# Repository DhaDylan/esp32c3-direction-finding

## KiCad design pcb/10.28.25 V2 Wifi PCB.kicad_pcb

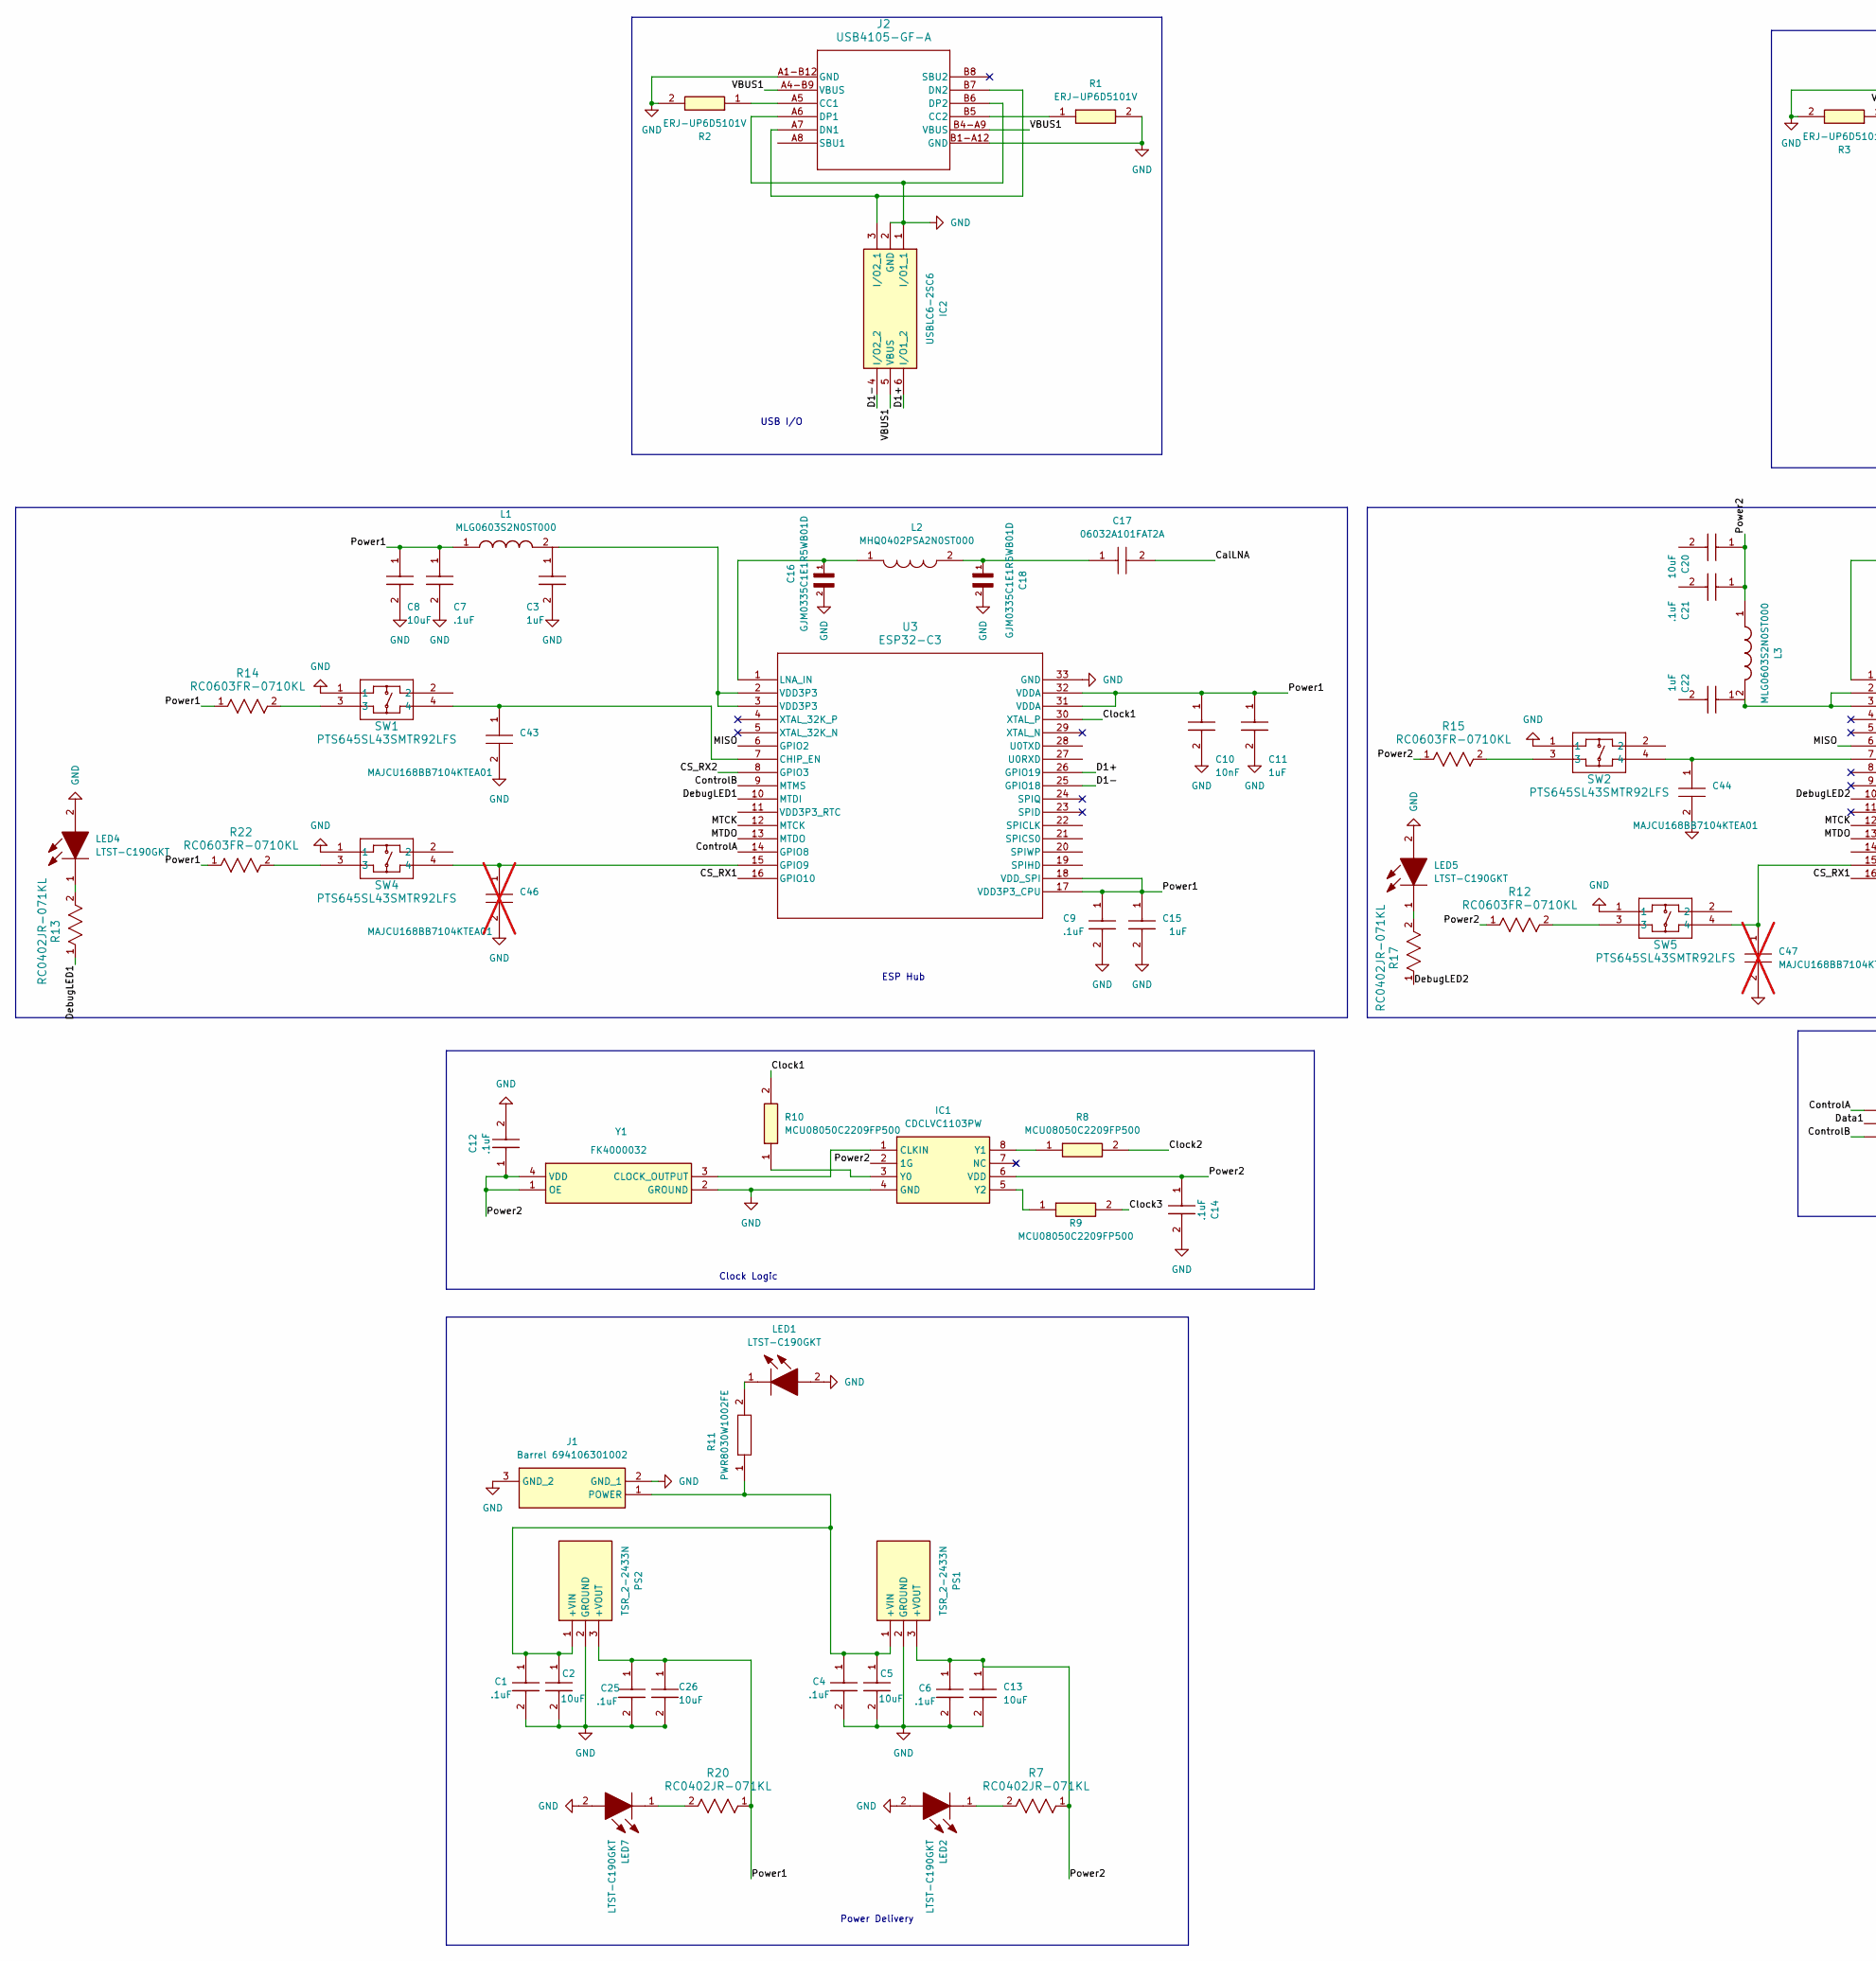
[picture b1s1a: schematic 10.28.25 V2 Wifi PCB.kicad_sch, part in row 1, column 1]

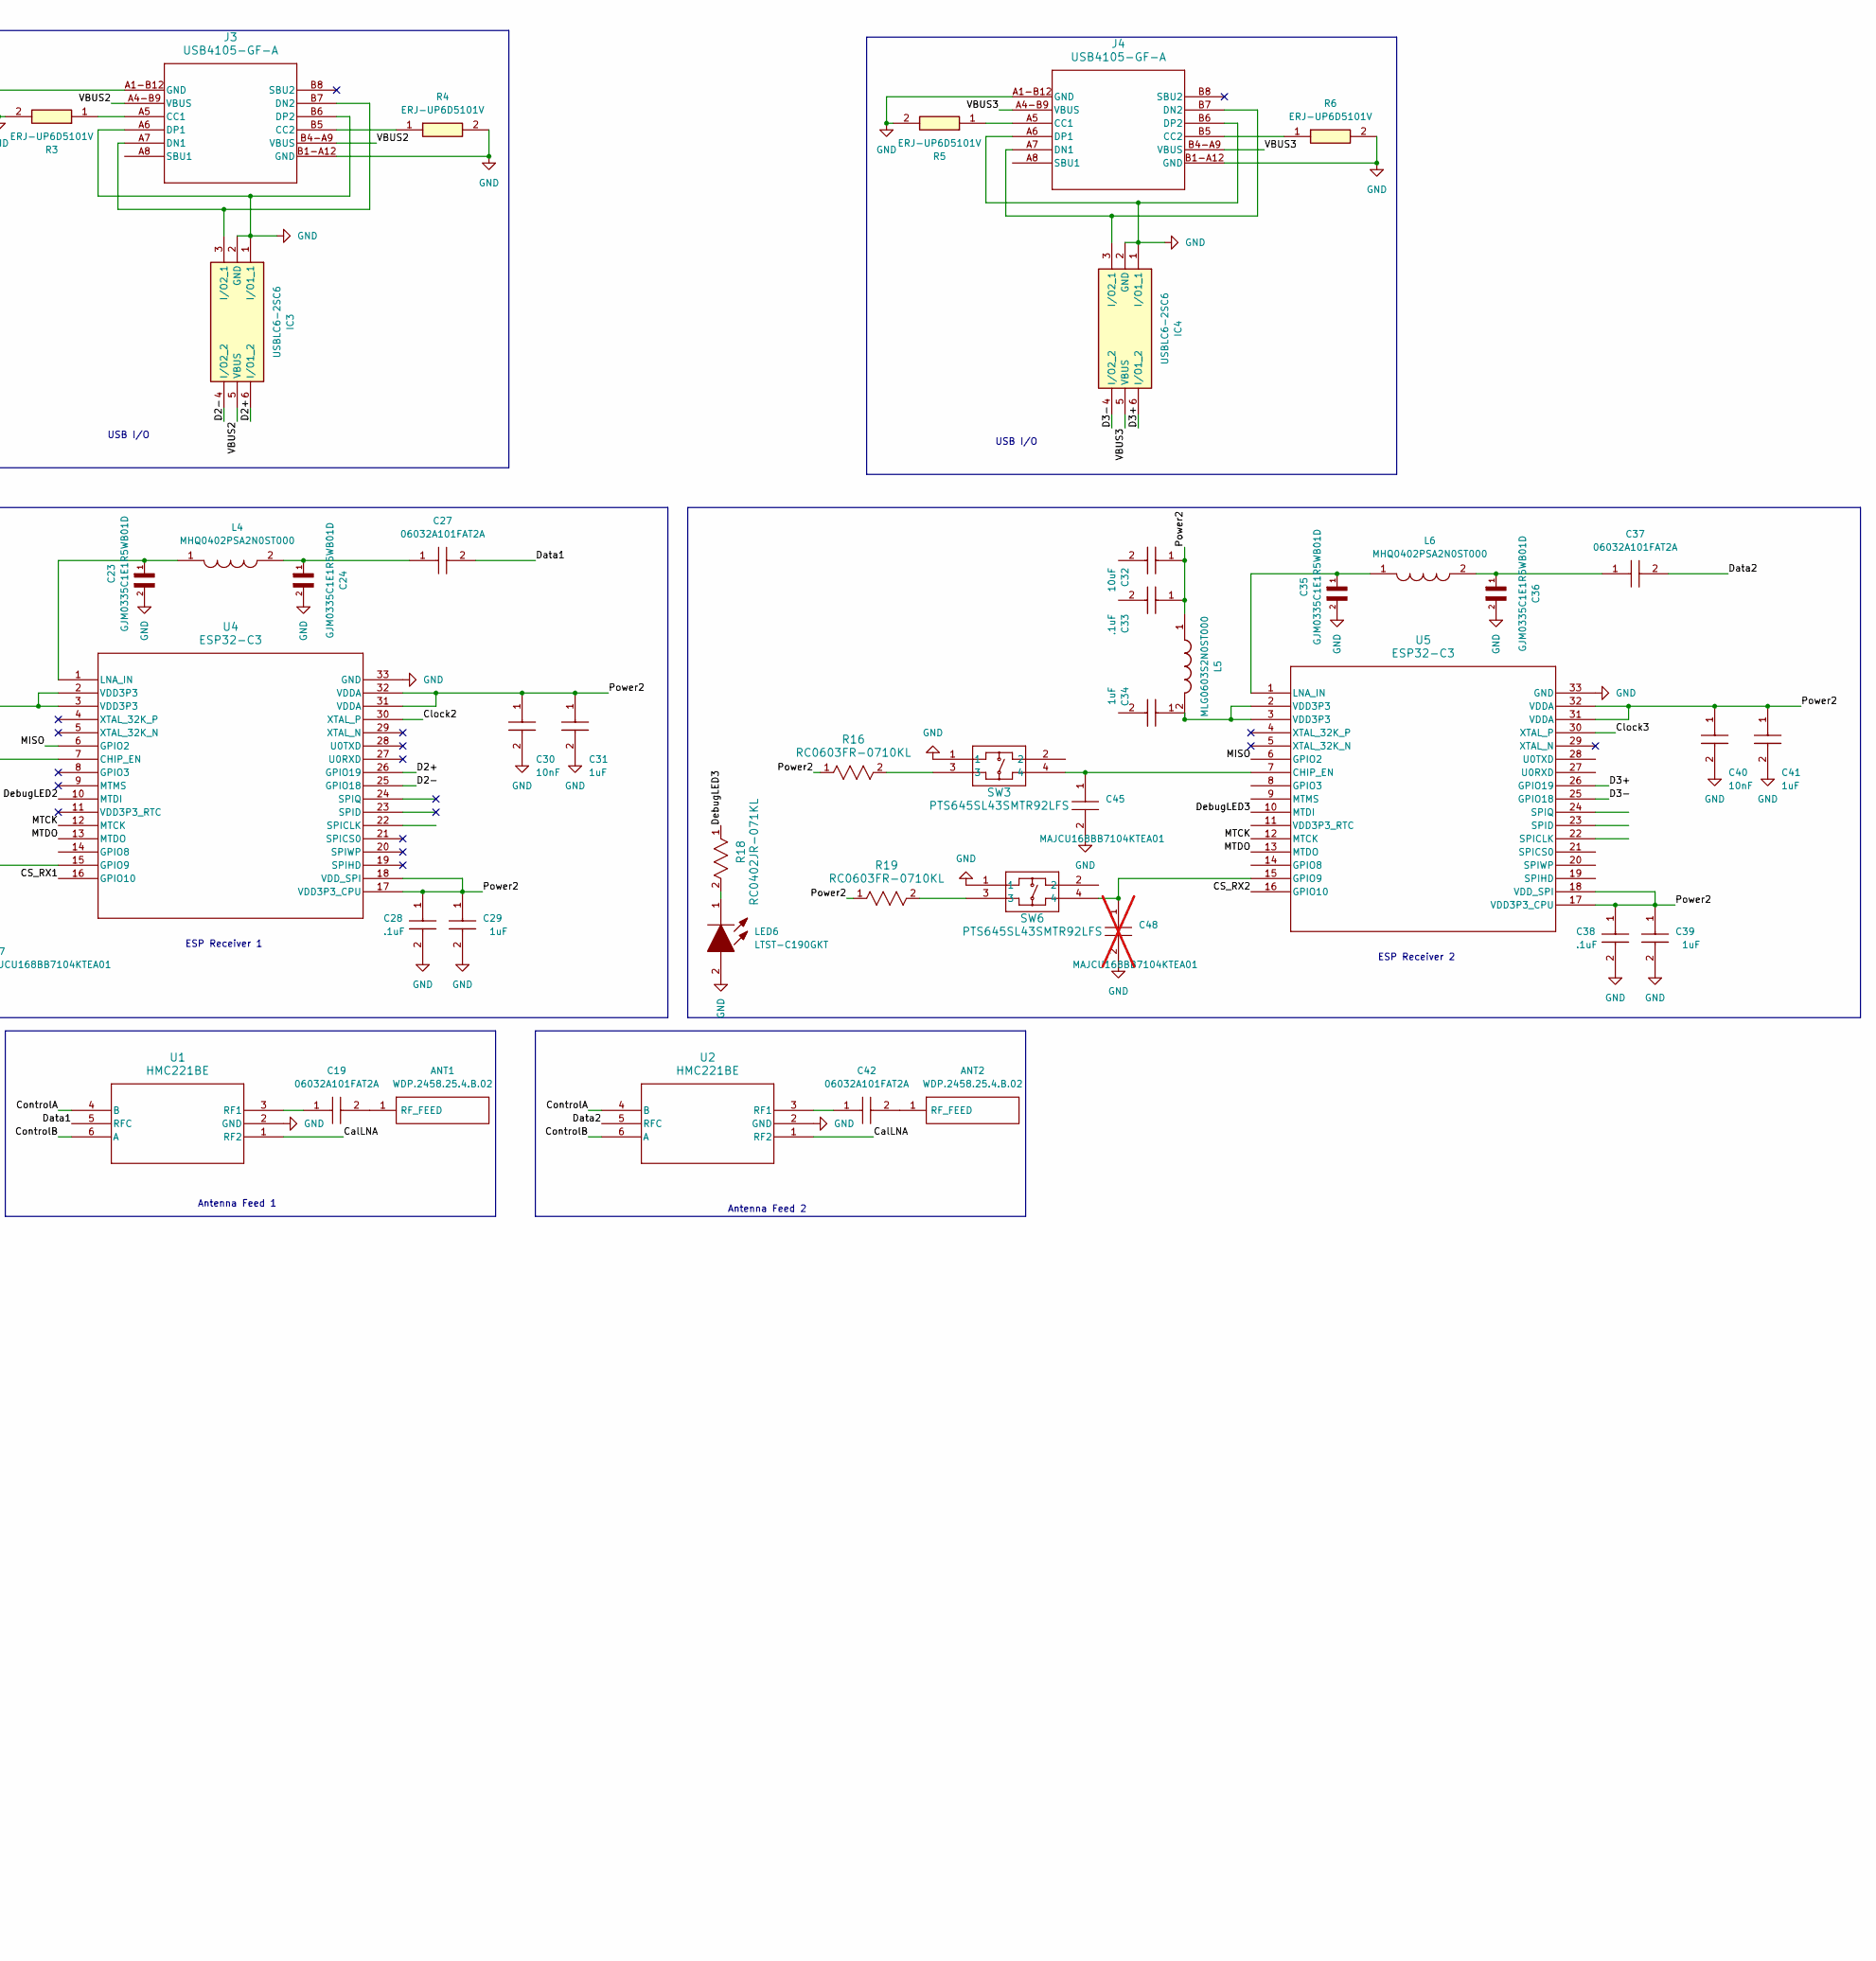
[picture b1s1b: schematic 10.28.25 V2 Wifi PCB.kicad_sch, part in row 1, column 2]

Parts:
ANT1, ANT2: WDP.2458.25.4.B.02; WDP2458254B02; Mouser Part Number 960-WDP.2458.25.4B02
C1, C4, C6, C7, C9, C12, C14, C21, C25, C28, C33, C38: .1uF; MBASx21x; Manufacturer_Part_Number MBASQ21GAB7104MTCA01
C2, C5, C8, C13, C20, C26, C32: 10uF; CAPC1608X80N; Mouser Part Number 810-C1608X7T1A106M08
C3, C11, C15, C22, C29, C31, C34, C39, C41: 1uF; CAPC1608X90N; Manufacturer_Part_Number CGA3E3X7R1H105K080AB
C10, C30, C40: 10nF; CAPC1608X90N; Mouser Part Number 581-0603YC103M4T2A
C16, C18, C23, C24, C35, C36: GJM0335C1E1R5WB01D; CAPC0603X33N
C17, C19, C27, C37, C42: 06032A101FAT2A; CAPC1608X90N; Mouser Part Number 581-06032A101FAT2A
C43, C44, C45: MAJCU168BB7104KTEA01; MAJx16; Manufacturer_Part_Number MAJCU168BB7104KTEA01
C46, C47, C48: MAJCU168BB7104KTEA01; MAJx16; Manufacturer_Part_Number MAJCU168BB7104KTEA01; not fitted
IC1: CDCLVC1103PW; SOP65P640X120-8N; Mouser Part Number 595-CDCLVC1103PW
IC2, IC3, IC4: USBLC6-2SC6; SOT95P280X145-6N; Mouser Part Number 511-USBLC6-2SC6
J1: Barrel 694106301002; 694106301002_1; Mouser Part Number 710-694106301002
J2, J3, J4: USB4105-GF-A; USB4105_GCT
L1, L3, L5: MLG0603S2N0ST000; MLG0603S; Manufacturer_Part_Number MLG0603S2N0ST000
L2, L4, L6: MHQ0402PSA2N0ST000; INDC0402X26N; Mouser Part Number 810-MHQ0402PSA2N0ST0
LED1, LED2, LED4, LED5, LED6, LED7: LTST-C190GKT; LEDC1608X90N; Mouser Part Number 859-LTST-C190GKT
PS1, PS2: TSR_2-2433N; TSR22433N; Manufacturer_Part_Number TSR 2-2433N
R1, R2, R3, R4, R5, R6: ERJ-UP6D5101V; ERJUP6; Mouser Part Number 667-ERJ-UP6D5101V
R7, R13, R17, R18, R20: RC0402JR-071KL; RC0402N_YAG
R8, R9, R10: MCU08050C2209FP500; RESC2012X55N; Mouser Part Number 594-MCU08050C2209FP5
R11: PWR8030W1002FE; RESM20876X785N; Mouser Part Number 652-PWR8030W1002FE
R12, R14, R15, R16, R19, R22: RC0603FR-0710KL; RC0603N_YAG
SW1, SW2, SW3, SW4, SW5, SW6: PTS645SL43SMTR92LFS; PTS645SL43SMTR92LFS_CNK
U1, U2: HMC221BE; RJ-6_ADI
U3, U4, U5: ESP32-C3; QFN32_5X5_EXP
Y1: FK4000032; Mouser Part Number 729-FK4000032

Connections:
/CS_RX1: U3.16 (GPIO10), U4.16 (GPIO10)
/CS_RX2: U3.8 (GPIO3), U5.16 (GPIO10)
/CalLNA: C17.2, U1.1 (RF2), U2.1 (RF2)
/Clock1: R10.2, U3.30 (XTAL_P)
/Clock2: R8.2, U4.30 (XTAL_P)
/Clock3: R9.2, U5.30 (XTAL_P)
/ControlA: U1.4 (B), U2.4 (B), U3.14 (GPIO8)
/ControlB: U1.6 (A), U2.6 (A), U3.9 (MTMS)
/D1+: IC2.6 (I/O1_2), U3.26 (GPIO19)
/D1-: IC2.4 (I/O2_2), U3.25 (GPIO18)
/D2+: IC3.6 (I/O1_2), U4.26 (GPIO19)
/D2-: IC3.4 (I/O2_2), U4.25 (GPIO18)
/D3+: IC4.6 (I/O1_2), U5.26 (GPIO19)
/D3-: IC4.4 (I/O2_2), U5.25 (GPIO18)
/Data1: C27.2, U1.5 (RFC)
/Data2: C37.2, U2.5 (RFC)
/DebugLED1: R13.1, U3.10 (MTDI)
/DebugLED2: R17.1, U4.10 (MTDI)
/DebugLED3: R18.1, U5.10 (MTDI)
/MISO: U3.6 (GPIO2), U4.6 (GPIO2), U5.6 (GPIO2)
/MTCK: U3.12 (MTCK), U4.12 (MTCK), U5.12 (MTCK)
/MTDO: U3.13 (MTDO), U4.13 (MTDO), U5.13 (MTDO)
/Power1: C7.1, C8.1, C9.1, C10.1, C11.1, C15.1, C25.1, C26.1, L1.1, PS2.3 (+VOUT), R14.1, R20.1, R22.1, U3.17 (VDD3P3_CPU), U3.18 (VDD_SPI), U3.31 (VDDA), U3.32 (VDDA)
/Power2: C6.1, C12.1, C13.1, C14.1, C20.1, C21.1, C28.1, C29.1, C30.1, C31.1, C32.1, C33.1, C38.1, C39.1, C40.1, C41.1, IC1.2 (1G), IC1.6 (VDD), L3.1, L5.1, PS1.3 (+VOUT), R7.1, R12.1, R15.1, R16.1, R19.1, U4.17 (VDD3P3_CPU), U4.18 (VDD_SPI), U4.31 (VDDA), U4.32 (VDDA), U5.17 (VDD3P3_CPU), U5.18 (VDD_SPI), U5.31 (VDDA), U5.32 (VDDA), Y1.1 (OE), Y1.4 (VDD)
/VBUS1: IC2.5 (VBUS), J2.A4-B9 (VBUS), J2.B4-A9 (VBUS)
/VBUS2: IC3.5 (VBUS), J3.A4-B9 (VBUS), J3.B4-A9 (VBUS)
/VBUS3: IC4.5 (VBUS), J4.A4-B9 (VBUS), J4.B4-A9 (VBUS)
GND: C1.2, C2.2, C3.2, C4.2, C5.2, C6.2, C7.2, C8.2, C9.2, C10.2, C11.2, C12.2, C13.2, C14.2, C15.2, C16.2, C18.2, C23.2, C24.2, C25.2, C26.2, C28.2, C29.2, C30.2, C31.2, C35.2, C36.2, C38.2, C39.2, C40.2, C41.2, C43.2, C44.2, C45.2, C46.2, C47.2, C48.2, IC1.4 (GND), IC2.1 (I/O1_1), IC2.2 (GND), IC3.1 (I/O1_1), IC3.2 (GND), IC4.1 (I/O1_1), IC4.2 (GND), J1.2 (GND_1), J1.3 (GND_2), J2.A1-B12 (GND), J2.A6 (DP1), J2.B1-A12 (GND), J2.B6 (DP2), J3.A1-B12 (GND), J3.A6 (DP1), J3.B1-A12 (GND), J3.B6 (DP2), J4.A1-B12 (GND), J4.A6 (DP1), J4.B1-A12 (GND), J4.B6 (DP2), LED1.2, LED2.2, LED4.2, LED5.2, LED6.2, LED7.2, PS1.2 (GROUND), PS2.2 (GROUND), R1.2, R2.2, R3.2, R4.2, R5.2, R6.2, SW1.1, SW2.1, SW3.1, SW4.1, SW5.1, SW6.1, U1.2 (GND), U2.2 (GND), U3.33 (GND), U4.33 (GND), U5.33 (GND), Y1.2 (GROUND)
unnamed: ANT1.1 (RF_FEED), C19.2
unnamed: ANT2.1 (RF_FEED), C42.2
unnamed: C17.1, C18.1, L2.2
unnamed: C22.1, L3.2, U4.2 (VDD3P3), U4.3 (VDD3P3)
unnamed: C24.1, C27.1, L4.2
unnamed: C34.1, L5.2, U5.2 (VDD3P3), U5.3 (VDD3P3)
unnamed: C36.1, C37.1, L6.2
unnamed: IC1.1 (CLKIN), Y1.3 (CLOCK_OUTPUT)
unnamed: IC1.3 (Y0), R10.1
unnamed: IC1.8 (Y1), R8.1
unnamed: IC1.5 (Y2), R9.1
unnamed: IC2.3 (I/O2_1), J2.A7 (DN1), J2.B7 (DN2)
unnamed: IC3.3 (I/O2_1), J3.A7 (DN1), J3.B7 (DN2)
unnamed: IC4.3 (I/O2_1), J4.A7 (DN1), J4.B7 (DN2)
unnamed: C1.1, C2.1, C4.1, C5.1, J1.1 (POWER), PS1.1 (+VIN), PS2.1 (+VIN), R11.1
unnamed: J2.A5 (CC1), R2.1
unnamed: J2.B5 (CC2), R1.1
unnamed: J3.A5 (CC1), R3.1
unnamed: J3.B5 (CC2), R4.1
unnamed: J4.A5 (CC1), R5.1
unnamed: J4.B5 (CC2), R6.1
unnamed: L1.2, U3.2 (VDD3P3), U3.3 (VDD3P3)
unnamed: LED1.1, R11.2
unnamed: LED2.1, R7.2
unnamed: LED4.1, R13.2
unnamed: LED5.1, R17.2
unnamed: LED6.1, R18.2
unnamed: LED7.1, R20.2
unnamed: R12.2, SW5.3
unnamed: R14.2, SW1.3
unnamed: R15.2, SW2.3
unnamed: R16.2, SW3.3
unnamed: R19.2, SW6.3
unnamed: R22.2, SW4.3
unnamed: C19.1, U1.3 (RF1)
unnamed: C42.1, U2.3 (RF1)
unnamed: C43.1, SW1.4, U3.7 (CHIP_EN)
unnamed: C46.1, SW4.4, U3.15 (GPIO9)
unnamed: C16.1, L2.1, U3.1 (LNA_IN)
unnamed: C44.1, SW2.4, U4.7 (CHIP_EN)
unnamed: C47.1, SW5.4, U4.15 (GPIO9)
unnamed: C23.1, L4.1, U4.1 (LNA_IN)
unnamed: C45.1, SW3.4, U5.7 (CHIP_EN)
unnamed: C48.1, SW6.4, U5.15 (GPIO9)
unnamed: C35.1, L6.1, U5.1 (LNA_IN)

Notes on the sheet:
Antenna Feed 1
USB I/O
Clock Logic
ESP Hub
Antenna Feed 2
ESP Receiver 2
ESP Receiver 1
Power Delivery

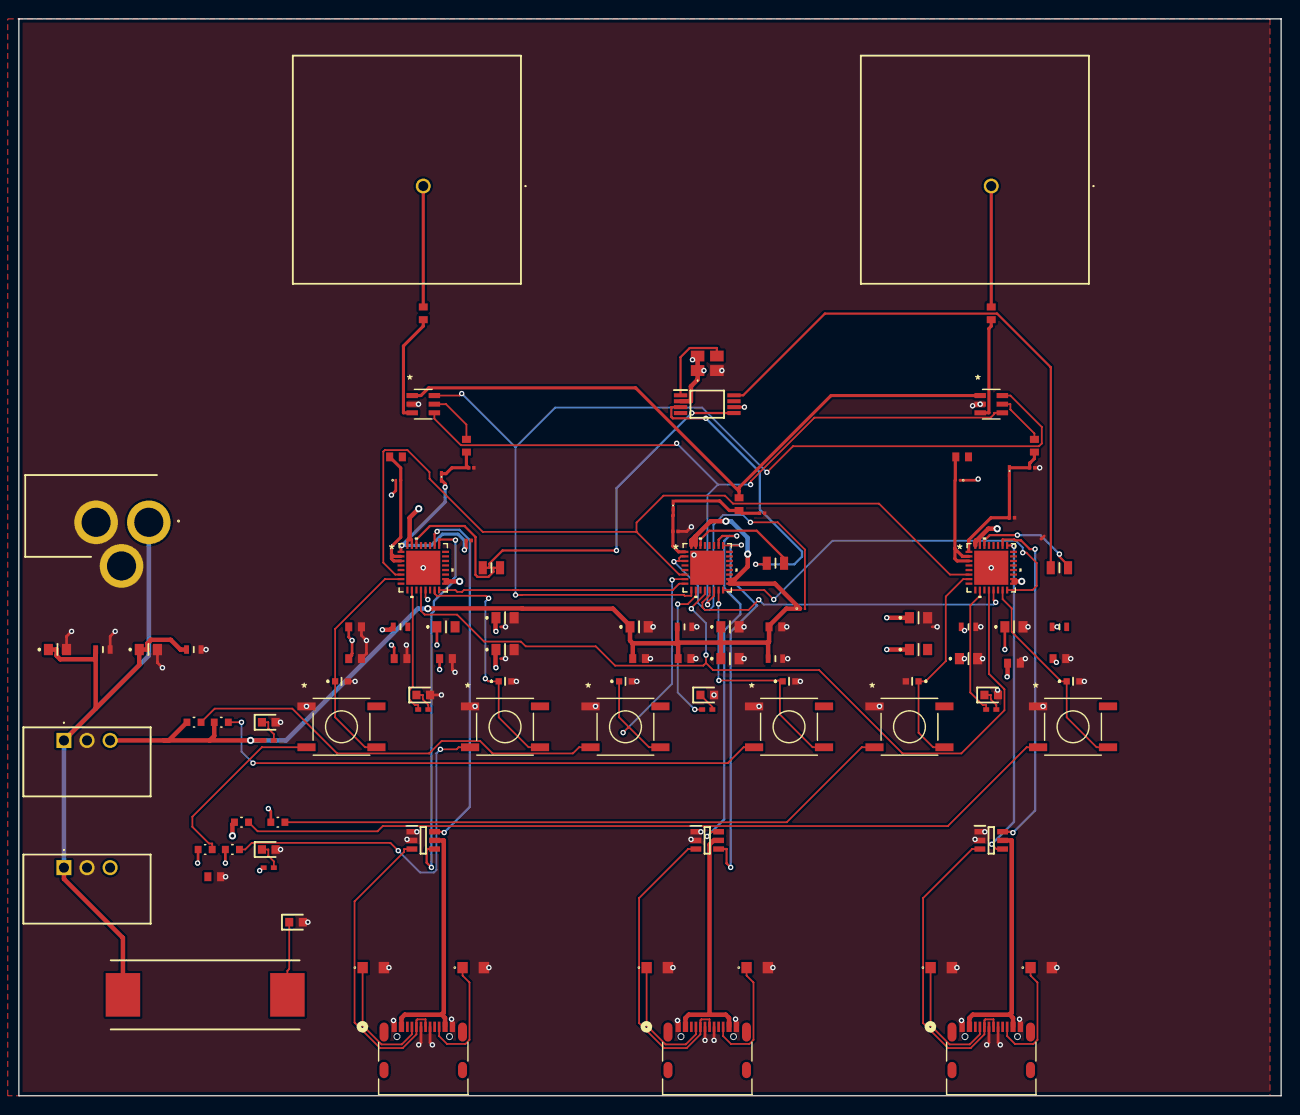
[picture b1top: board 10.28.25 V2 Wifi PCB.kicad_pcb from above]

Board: 4 copper layers, 138.9 x 118.5 mm, 105 parts (0 on the bottom side), 73 nets.

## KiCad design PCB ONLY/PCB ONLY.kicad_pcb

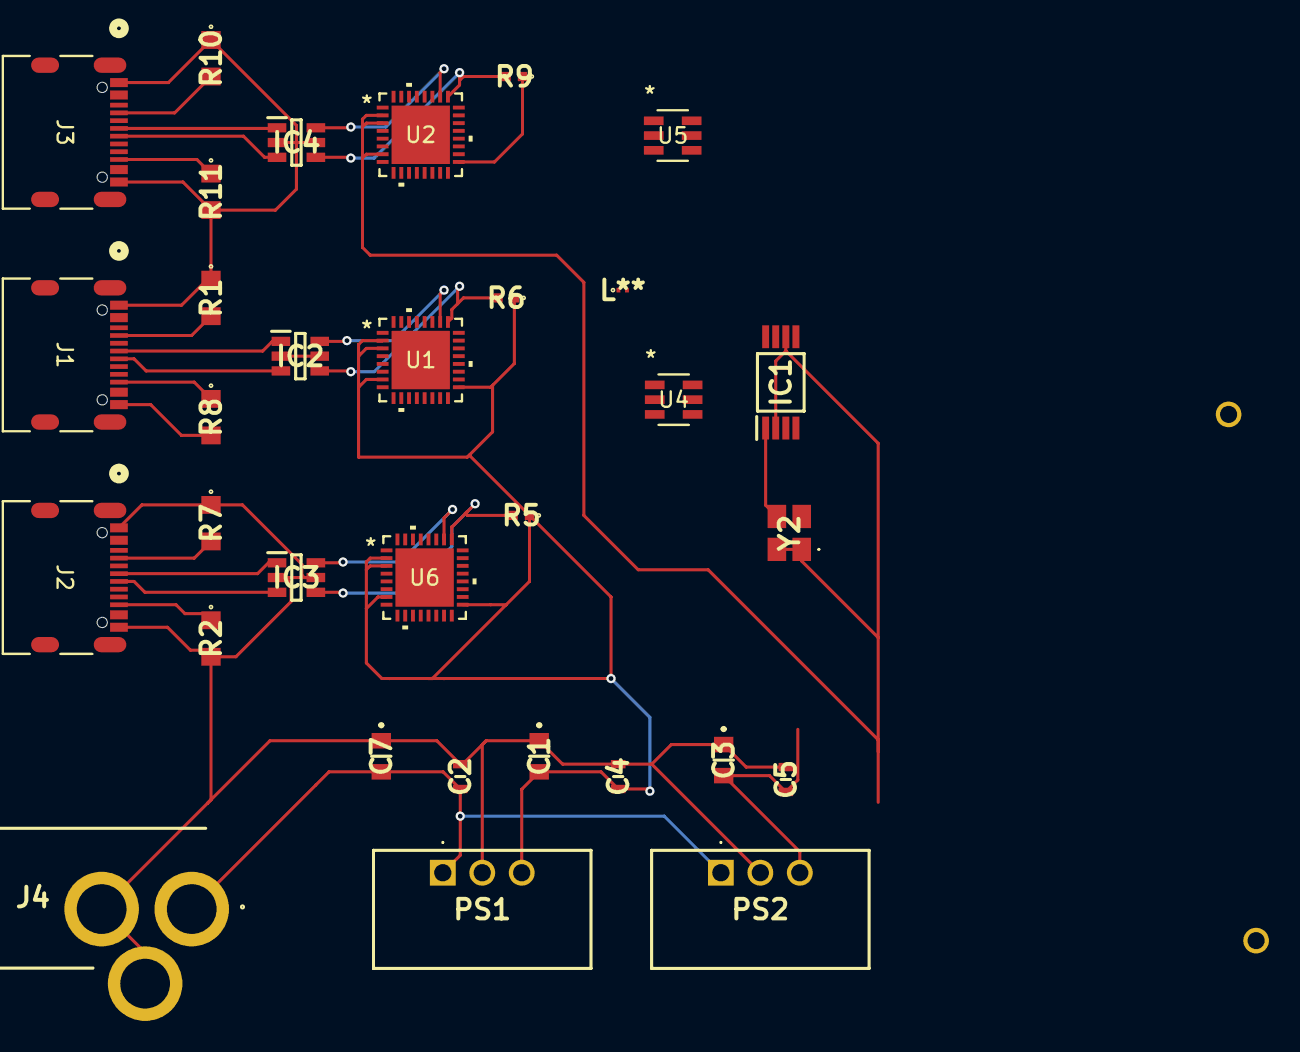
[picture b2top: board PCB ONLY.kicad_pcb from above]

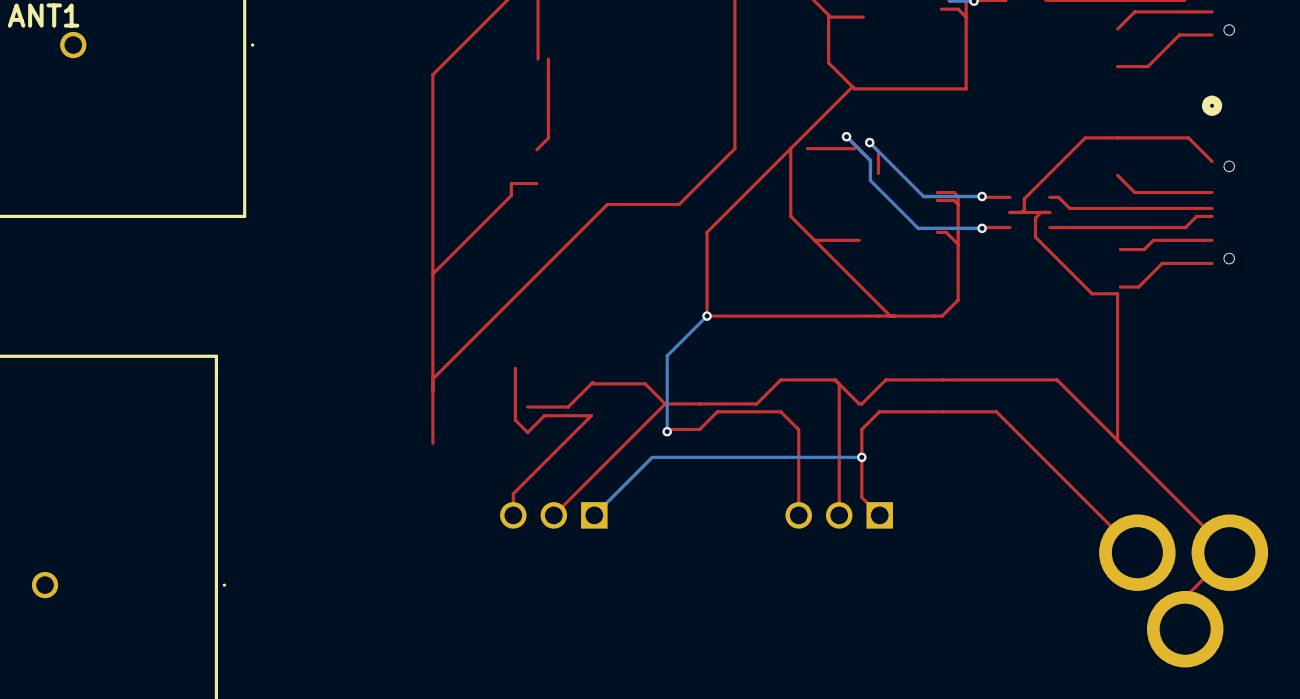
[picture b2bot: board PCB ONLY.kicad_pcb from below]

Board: 2 copper layers, 34 parts (2 on the bottom side), 33 nets.

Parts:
ANT1, ANT2: WDP.2458.25.4.B.02; WDP2458254B02
C1, C3, C7: .1uF; MBASx21x
C2, C4, C5: 10uF; CAPC1608X80N
IC1: CDCLVC1103PW Clk Buf; SOP65P640X120-8N
IC2, IC3, IC4: USBLC6-2SC6; SOT95P280X145-6N
J1, J2, J3: USB4105-GF-A; USB4105_GCT
J4: 694106301002 Barrel; 694106301002_1
L**: MLG0603S
PS1, PS2: TSR_2-2433N Buck; TSR22433N
R1, R2, R7, R8, R10, R11: 5.1k ERJ-UP6D5101V; ERJUP6
R5, R6, R9: 1.5k RCC04021K50FKED; RCC0402_e3
U1, U2, U6: ESP32-C3; QFN32_5X5_EXP
U4: HMC221BE RF Sw; RJ-6_ADI
U5: HMC221BE; RJ-6_ADI
Y2: FK4000032 Crystal; FK4000032

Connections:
GND: C1.1, C2.1, C3.1, C4.1, C5.1, C7.1, IC1.4 (GND), IC2.2 (GND), IC2.5 (VBUS), IC3.2 (GND), IC3.5 (VBUS), IC4.2 (GND), IC4.5 (VBUS), J1.A1-B12 (GND), J1.B1-A12 (GND), J2.A1-B12 (GND), J2.B1-A12 (GND), J3.A1-B12 (GND), J3.B1-A12 (GND), J4.2 (GND_1), J4.3 (GND_2), PS1.2 (GROUND), PS2.2 (GROUND), R1.1, R2.2, R7.1, R8.2, R10.1, R11.2, U1.33 (GND), U2.33 (GND), U4.2 (GND), U5.2 (GND), U6.33 (GND), Y2.2 (GROUND)
unnamed: ANT1.1 (RF_FEED), U4.3 (RF1)
unnamed: ANT2.1 (RF_FEED), U5.3 (RF1)
unnamed: C3.2, C5.2, IC1.2 (1G), IC1.6 (VDD), PS2.3 (+VOUT), R9.1, U2.2 (VDD3P3), U2.3 (VDD3P3), U2.7 (CHIP_EN), U2.17 (VDD3P3_CPU), U2.18 (VDD_SPI), U2.31 (VDDA), U2.32 (VDDA), Y2.1 (OE), Y2.4 (VDD)
unnamed: IC1.1 (CLKIN), Y2.3 (CLOCK_OUTPUT)
unnamed: IC1.3 (Y0), U6.30 (XTAL_P)
unnamed: IC1.8 (Y1), U1.30 (XTAL_P)
unnamed: IC1.5 (Y2), U2.30 (XTAL_P)
unnamed: IC2.1 (I/O1_1), J1.A6 (DP1)
unnamed: IC2.6 (I/O1_2), U1.26 (GPIO19)
unnamed: IC2.3 (I/O2_1), J1.A7 (DN1)
unnamed: IC2.4 (I/O2_2), R6.2, U1.25 (GPIO18)
unnamed: IC3.1 (I/O1_1), J2.A6 (DP1)
unnamed: IC3.6 (I/O1_2), U6.26 (GPIO19)
unnamed: IC3.3 (I/O2_1), J2.A7 (DN1)
unnamed: IC3.4 (I/O2_2), R5.2, U6.25 (GPIO18)
unnamed: IC4.1 (I/O1_1), J3.A6 (DP1)
unnamed: IC4.6 (I/O1_2), U2.26 (GPIO19)
unnamed: IC4.3 (I/O2_1), J3.A7 (DN1)
unnamed: IC4.4 (I/O2_2), R9.2, U2.25 (GPIO18)
unnamed: J1.A5 (CC1), R1.2
unnamed: J1.B5 (CC2), R8.1
unnamed: J2.A5 (CC1), R7.2
unnamed: J2.B5 (CC2), R2.1
unnamed: J3.A5 (CC1), R10.2
unnamed: J3.B5 (CC2), R11.1
unnamed: C2.2, C7.2, J4.1 (POWER), PS1.1 (+VIN), PS2.1 (+VIN)
unnamed: C1.2, C4.2, PS1.3 (+VOUT), R5.1, R6.1, U1.2 (VDD3P3), U1.3 (VDD3P3), U1.7 (CHIP_EN), U1.17 (VDD3P3_CPU), U1.18 (VDD_SPI), U1.31 (VDDA), U1.32 (VDDA), U6.2 (VDD3P3), U6.3 (VDD3P3), U6.7 (CHIP_EN), U6.17 (VDD3P3_CPU), U6.31 (VDDA), U6.32 (VDDA)
unnamed: U1.1 (LNA_IN), U4.5 (RFC)
unnamed: U2.1 (LNA_IN), U5.5 (RFC)
unnamed: U4.6 (A), U5.6 (A), U6.16 (GPIO10)
unnamed: U4.4 (B), U5.4 (B), U6.15 (GPIO9)
unnamed: U4.1 (RF2), U5.1 (RF2), U6.1 (LNA_IN)
